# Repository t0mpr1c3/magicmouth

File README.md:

magicmouth
==========

Arduino speech shield http://www.tinyurl.com/magicmouth/

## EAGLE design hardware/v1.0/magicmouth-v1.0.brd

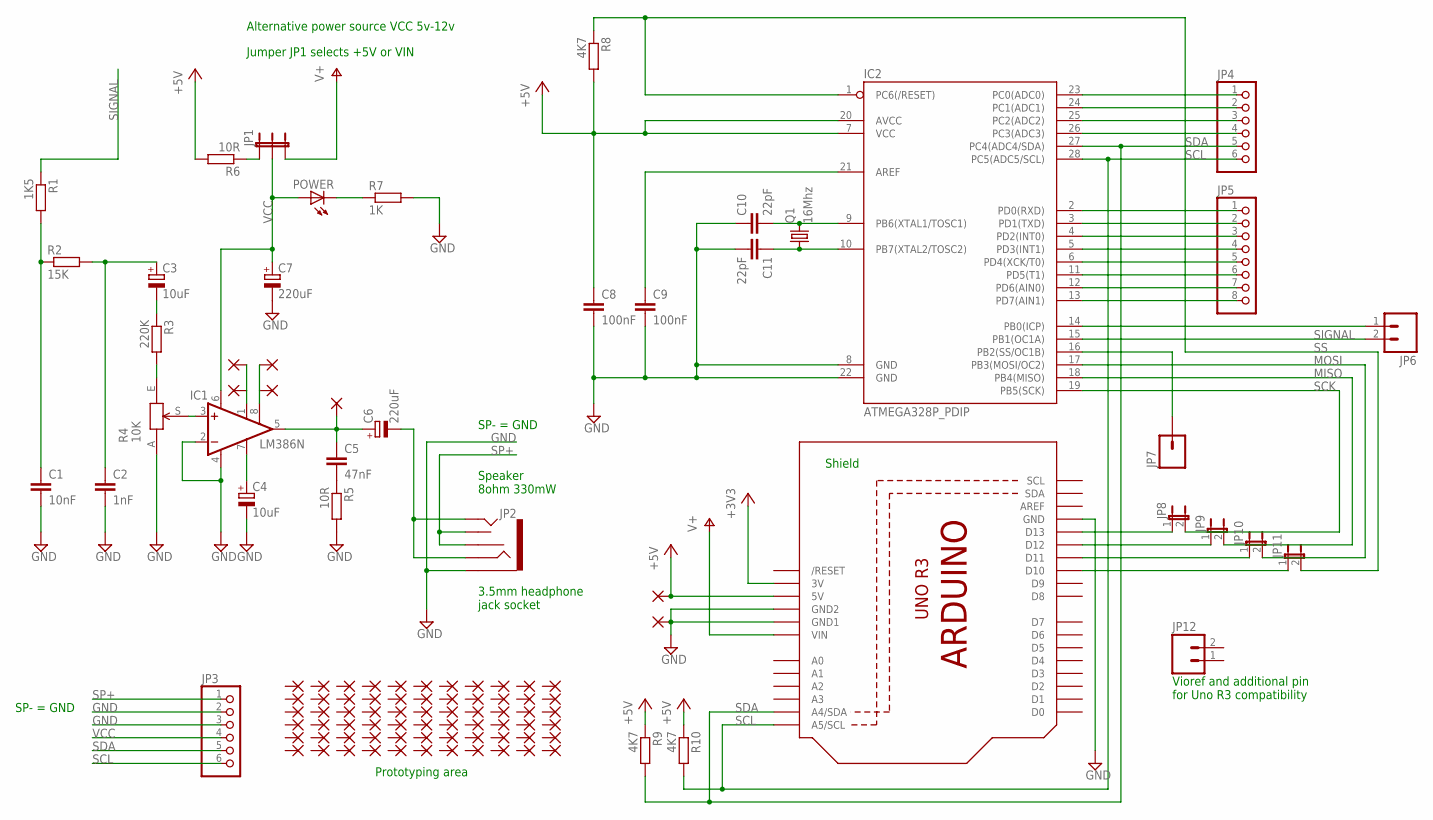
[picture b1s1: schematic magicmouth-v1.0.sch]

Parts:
C1: 10nF; C050-025X075
C2: 1nF; C050-025X075
C3, C4: 10uF; E2,5-7
C5: 47nF; C050-025X075
C6, C7: 220uF; TT2D7
C8, C9: 100nF; C025-025X050
C10, C11: 22pF; C025-025X050
IC1: LM386N; DIL08
IC2: ATMEGA328P_PDIP; DIL28-3
JP1: JUMPER-3PTH; 1X03
JP2: AUDIO-JACK2PTH; AUDIO-JACK
JP3, JP4: PINHD-1X6CB; 1X06-CLEANBIG
JP5: PINHD-1X8CLEANBIG; 1X08-CLEANBIG
JP6, JP12: M021X02_NO_SILK; 1X02_NO_SILK
JP7: M01SMDNS; 1X01NS
JP8, JP9, JP10, JP11: JUMPER-2PTH; 1X02
P1, P5, P8: 1,6/0,8
PAD1, PAD3, PAD7, PAD8, PAD9, PAD10, PAD11, PAD12, PAD13, PAD14, PAD15, PAD16, PAD17, PAD18, PAD19, PAD20, PAD21, PAD22, PAD23, PAD24, PAD25, PAD26, PAD27, PAD28, PAD29, PAD30, PAD31, PAD32, PAD33, PAD34, PAD35, PAD36, PAD37, PAD38, PAD39, PAD40, PAD41, PAD42, PAD43, PAD44, PAD45, PAD46, PAD47, PAD48, PAD49, PAD50, PAD51, PAD52, PAD53, PAD54, PAD55, PAD56, PAD57, PAD58, PAD59, PAD60, PAD61, PAD62, PAD63, PAD64, PAD65, PAD66, PAD67, PAD68, PAD69, PAD70, PAD71, PAD72, PAD73, PAD74: 1,6/0,8
POWER: LED3MM
Q1: 16Mhz; HC49/S
R1: 1K5; 0207/7
R2: 15K; 0207/7
R3: 220K; 0207/7
R4: 10K; 3352T
R5, R6: 10R; 0207/7
R7: 1K; 0207/7
R8, R9, R10: 4K7; 0207/7
U1: ARDUINOR3-NOIOREF-NOTEXT; ARDUINOR3-NOTEXT-NOIOREF

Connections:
+3V3: U1.3V
+5V: C8.1, IC2.7 (VCC), IC2.20 (AVCC), PAD55.1, R6.2, R8.2, R9.1, R10.1, U1.5V
D8: IC2.14 (PB0(ICP)), JP6.1
GND: C1.2, C2.2, C4.-, C7.-, C8.2, C9.2, C10.1, C11.2, IC1.2 (-IN), IC1.4 (GND), IC2.8 (GND), IC2.22 (GND), JP2.SLEEVE, JP3.2, JP3.3, PAD68.1, R4.A, R5.2, R7.2, U1.GND, U1.GND1, U1.GND2
MISO: IC2.18 (PB4(MISO)), JP9.2
MOSI: IC2.17 (PB3(MOSI/OC2)), JP10.2
unnamed: C5.1, C6.+, IC1.5 (OUT), P5.1
unnamed: C1.1, R1.2, R2.1
unnamed: C9.1, IC2.21 (AREF)
unnamed: C5.2, R5.1
unnamed: R3.2, R4.E
unnamed: C10.2, IC2.9 (PB6(XTAL1/TOSC1)), Q1.2
unnamed: JP1.1, R6.1
unnamed: C6.-, JP2.RING, JP2.TIP
unnamed: IC1.3 (+IN), R4.S
unnamed: POWER.K (C), R7.1
unnamed: C11.1, IC2.10 (PB7(XTAL2/TOSC2)), Q1.1
unnamed: IC2.16 (PB2(SS/OC1B)), JP7.1
unnamed: IC2.23 (PC0(ADC0)), JP4.1
unnamed: C2.1, C3.+, R2.2
unnamed: IC2.24 (PC1(ADC1)), JP4.2
unnamed: IC2.2 (PD0(RXD)), JP5.1
unnamed: IC2.3 (PD1(TXD)), JP5.2
unnamed: IC2.4 (PD2(INT0)), JP5.3
unnamed: IC2.5 (PD3(INT1)), JP5.4
unnamed: IC2.6 (PD4(XCK/T0)), JP5.5
unnamed: IC2.11 (PD5(T1)), JP5.6
unnamed: IC2.12 (PD6(AIN0)), JP5.7
unnamed: IC2.13 (PD7(AIN1)), JP5.8
unnamed: C4.+, IC1.7 (BYPASS)
unnamed: IC2.25 (PC2(ADC2)), JP4.3
unnamed: IC2.26 (PC3(ADC3)), JP4.4
unnamed: IC1.1 (GAIN), P1.1, PAD1.1
unnamed: C3.-, R3.1
unnamed: JP8.1, U1.D13
unnamed: JP9.1, U1.D12
unnamed: JP10.1, U1.D11
unnamed: JP11.1, U1.D10
unnamed: IC1.8 (GAIN), P8.1, PAD3.1
SCK: IC2.19 (PB5(SCK)), JP8.2
SCL: IC2.28 (PC5(ADC5/SCL)), JP3.6, JP4.6, R10.2, U1.A5 (A5/SCL)
SDA: IC2.27 (PC4(ADC4/SDA)), JP3.5, JP4.5, R9.2, U1.A4 (A4/SDA)
SIGNAL: IC2.15 (PB1(OC1A)), JP6.2, R1.1
SP+: JP2.RSH, JP2.TSH, JP3.1
SS: IC2.1 (PC6(/RESET)), JP11.2, R8.1
VCC: C7.+, IC1.6 (VS), JP1.2, JP3.4, POWER.A
VIN: JP1.3, U1.VIN

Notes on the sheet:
Speaker 8ohm 330mW
Jumper JP1 selects +5V or VIN
Alternative power source VCC 5v-12v
Shield
3.5mm headphone jack socket
Prototyping area
SP- = GND
Vioref and additional pin for Uno R3 compatibility

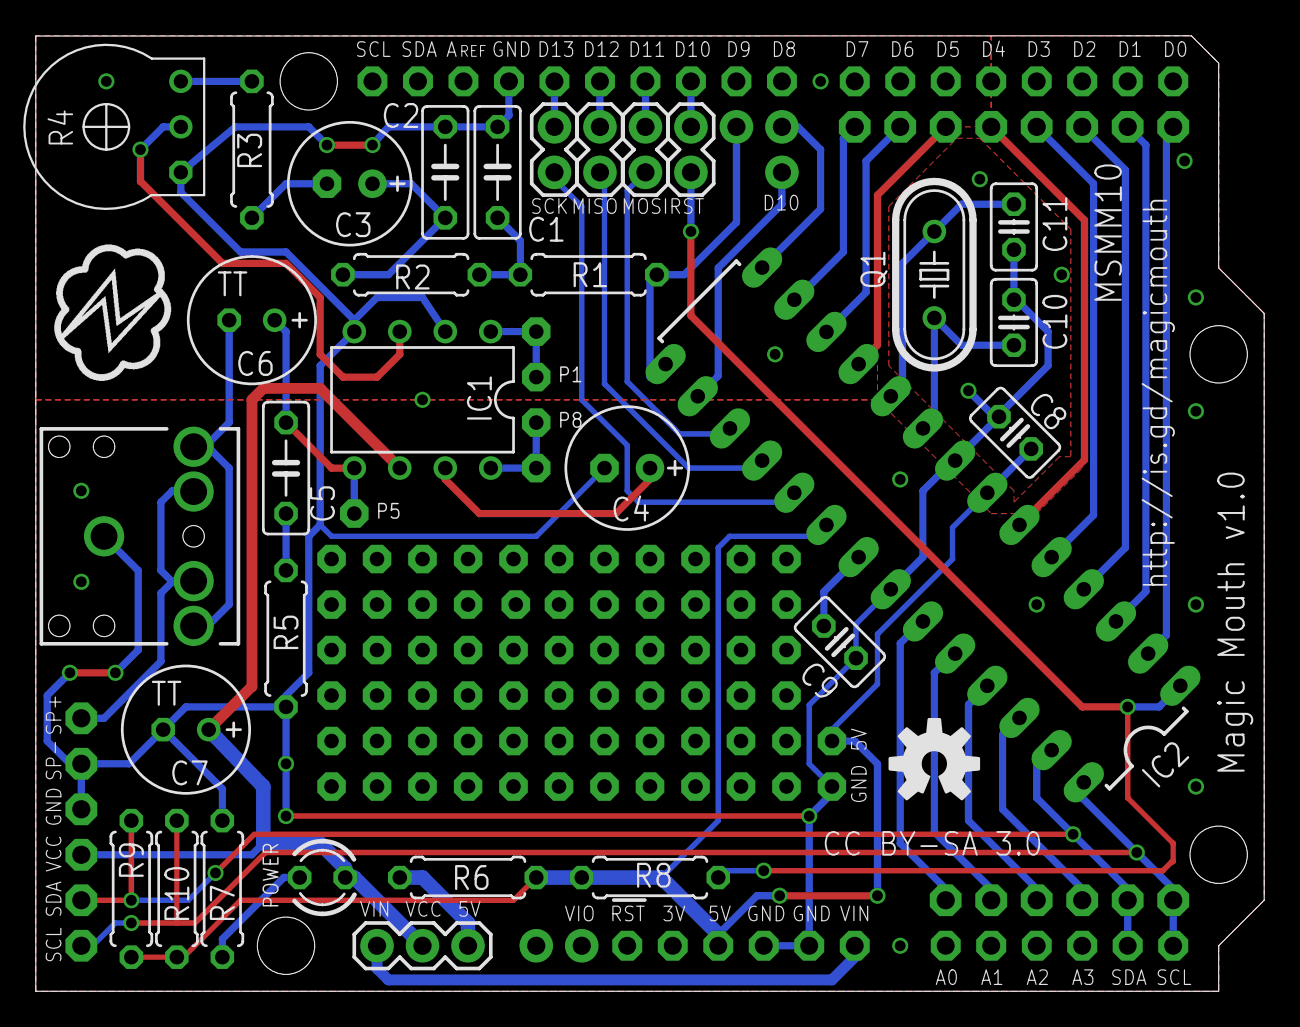
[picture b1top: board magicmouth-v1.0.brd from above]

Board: 2 copper layers, 68.6 x 53.3 mm, 113 parts (1 on the bottom side), 46 nets.

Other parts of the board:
U$1, U$2: OSHW-LOGO-M

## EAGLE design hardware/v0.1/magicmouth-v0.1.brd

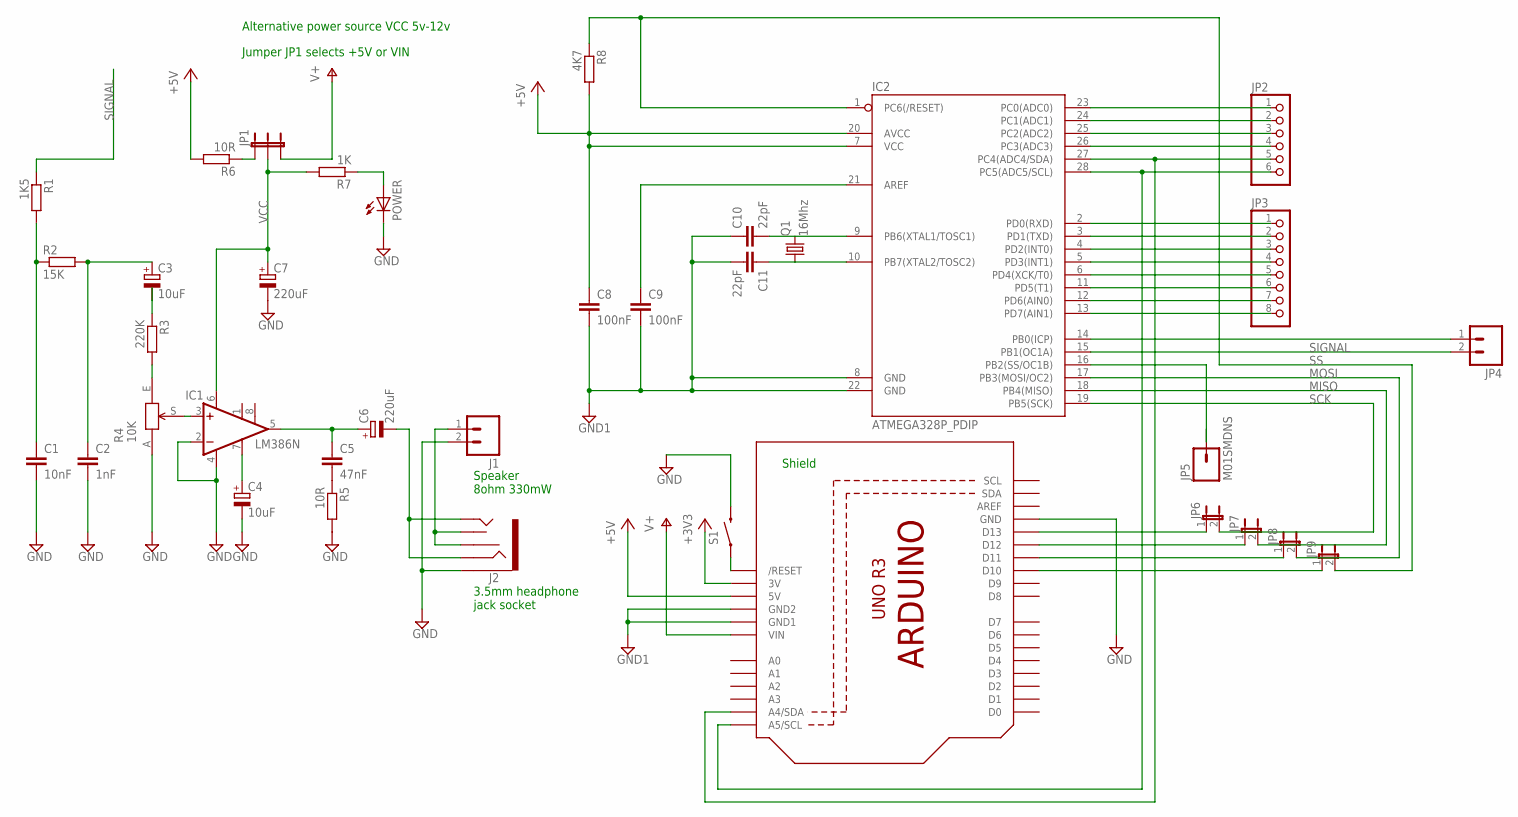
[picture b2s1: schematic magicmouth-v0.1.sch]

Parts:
C1: 10nF; C050-025X075
C2: 1nF; C050-025X075
C3, C4: 10uF; E2,5-7
C5: 47nF; C050-025X075
C6, C7: 220uF; TT5D7L
C8, C9: 100nF; C025-025X050
C10, C11: 22pF; C025-025X050
IC1: LM386N; DIL08
IC2: ATMEGA328P_PDIP; DIL28-3
J1: M023.5MM; SCREWTERMINAL-3.5MM-2
J2: AUDIO-JACK2PTH; AUDIO-JACK
JP1: JUMPER-3PTH; 1X03
JP2: PINHD-1X6CB; 1X06-CLEANBIG
JP3: PINHD-1X8CLEANBIG; 1X08-CLEANBIG
JP4: M021X02_NO_SILK; 1X02_NO_SILK
JP5: M01SMDNS; 1X01NS
JP6, JP7, JP8, JP9: JUMPER-2PTH; 1X02
POWER: LED3MM
Q1: 16Mhz; HC49/S
R1: 1K5; 0207/7
R2: 15K; 0207/7
R3: 220K; 0207/7
R4: 10K; 3352T
R5, R6: 10R; 0207/7
R7: 1K; 0207/7
R8: 4K7; 0207/7
S1: SWITCH-MOMENTARY-2PTH; TACTILE-PTH
U1: ARDUINOR3-NOIOREF-NOTEXT; ARDUINOR3-NOTEXT-NOIOREF

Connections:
+3V3: U1.3V
+5V: C8.1, IC2.7 (VCC), IC2.20 (AVCC), R6.2, R8.2, U1.5V
GND: C1.2, C2.2, C4.-, C7.-, IC1.2 (-IN), IC1.4 (GND), J1.2, J2.SLEEVE, POWER.K (C), R4.A, R5.2, S1.3 (2), U1.GND
GND1: C8.2, C9.2, C10.1, C11.2, IC2.8 (GND), IC2.22 (GND), U1.GND1, U1.GND2
MISO: IC2.18 (PB4(MISO)), JP7.2
MOSI: IC2.17 (PB3(MOSI/OC2)), JP8.2
unnamed: C5.1, C6.+, IC1.5 (OUT)
unnamed: C1.1, R1.2, R2.1
unnamed: J1.1, J2.RSH, J2.TSH
unnamed: C5.2, R5.1
unnamed: C3.-, R3.1
unnamed: C10.2, IC2.9 (PB6(XTAL1/TOSC1)), Q1.2
unnamed: JP1.1, R6.1
unnamed: C6.-, J2.RING, J2.TIP
unnamed: IC1.3 (+IN), R4.S
unnamed: POWER.A, R7.1
unnamed: C11.1, IC2.10 (PB7(XTAL2/TOSC2)), Q1.1
unnamed: IC2.16 (PB2(SS/OC1B)), JP5.1
unnamed: IC2.23 (PC0(ADC0)), JP2.1
unnamed: IC2.24 (PC1(ADC1)), JP2.2
unnamed: IC2.25 (PC2(ADC2)), JP2.3
unnamed: IC2.2 (PD0(RXD)), JP3.1
unnamed: IC2.3 (PD1(TXD)), JP3.2
unnamed: IC2.4 (PD2(INT0)), JP3.3
unnamed: IC2.5 (PD3(INT1)), JP3.4
unnamed: IC2.6 (PD4(XCK/T0)), JP3.5
unnamed: IC2.11 (PD5(T1)), JP3.6
unnamed: IC2.12 (PD6(AIN0)), JP3.7
unnamed: IC2.13 (PD7(AIN1)), JP3.8
unnamed: IC2.14 (PB0(ICP)), JP4.1
unnamed: JP6.1, U1.D13
unnamed: JP7.1, U1.D12
unnamed: IC2.26 (PC3(ADC3)), JP2.4
unnamed: JP8.1, U1.D11
unnamed: JP9.1, U1.D10
unnamed: IC2.27 (PC4(ADC4/SDA)), JP2.5, U1.A4 (A4/SDA)
unnamed: IC2.28 (PC5(ADC5/SCL)), JP2.6, U1.A5 (A5/SCL)
unnamed: C2.1, C3.+, R2.2
unnamed: C4.+, IC1.7 (BYPASS)
unnamed: C9.1, IC2.21 (AREF)
unnamed: S1.1, U1.RESET (/RESET)
unnamed: R3.2, R4.E
SCK: IC2.19 (PB5(SCK)), JP6.2
SIGNAL: IC2.15 (PB1(OC1A)), JP4.2, R1.1
SS: IC2.1 (PC6(/RESET)), JP9.2, R8.1
VCC: C7.+, IC1.6 (VS), JP1.2, R7.2
VIN: JP1.3, U1.VIN

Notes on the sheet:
Speaker 8ohm 330mW
Jumper JP1 selects +5V or VIN
Alternative power source VCC 5v-12v
Shield
3.5mm headphone jack socket

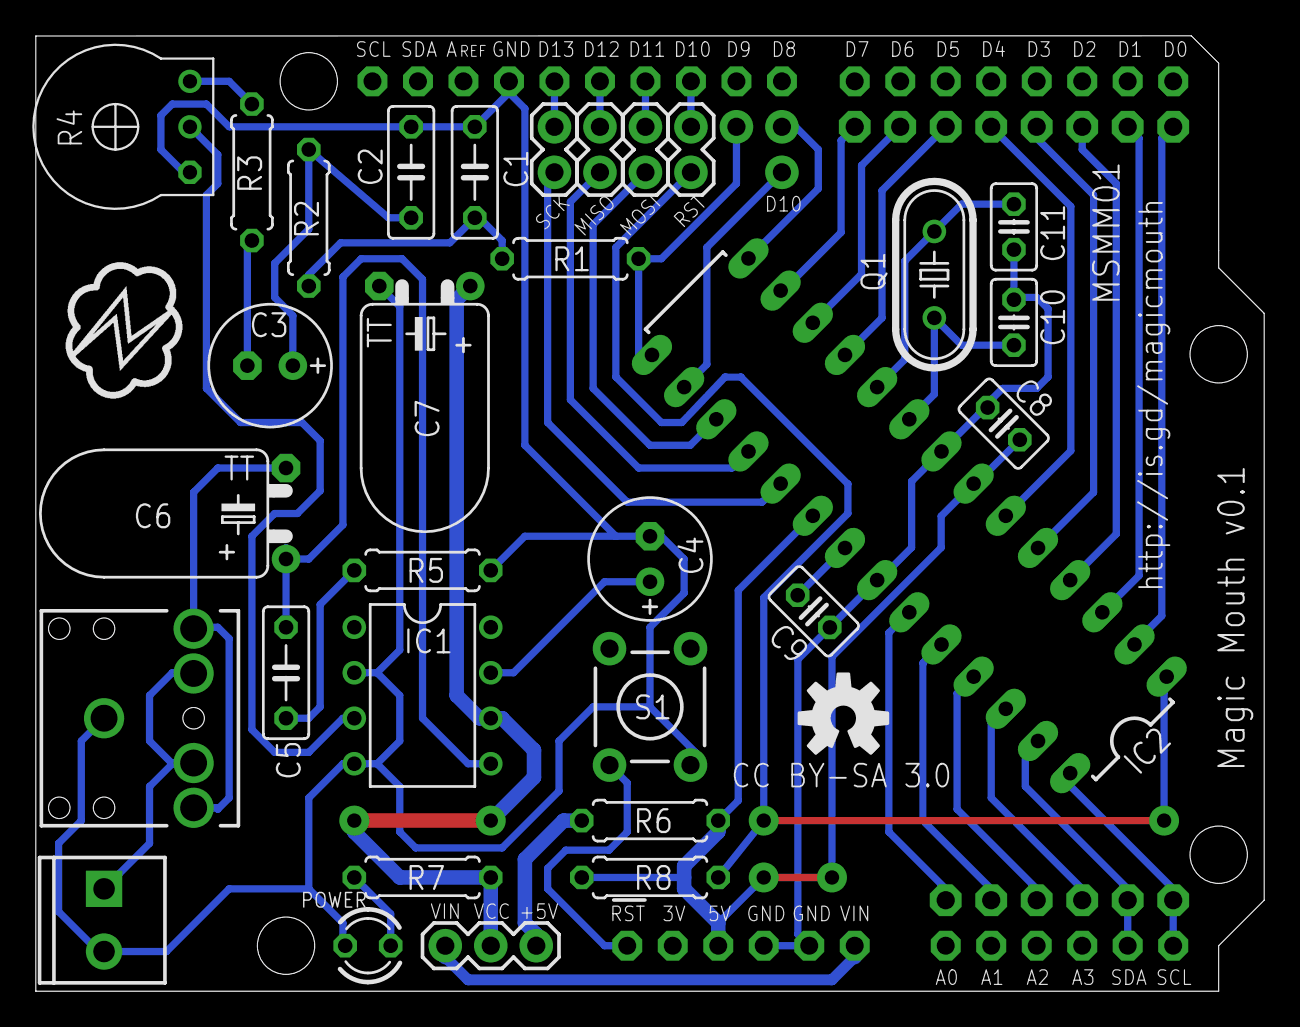
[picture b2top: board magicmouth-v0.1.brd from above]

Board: 2 copper layers, 68.6 x 53.3 mm, 37 parts (0 on the bottom side), 46 nets.

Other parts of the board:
U$1: OSHW-LOGO-M

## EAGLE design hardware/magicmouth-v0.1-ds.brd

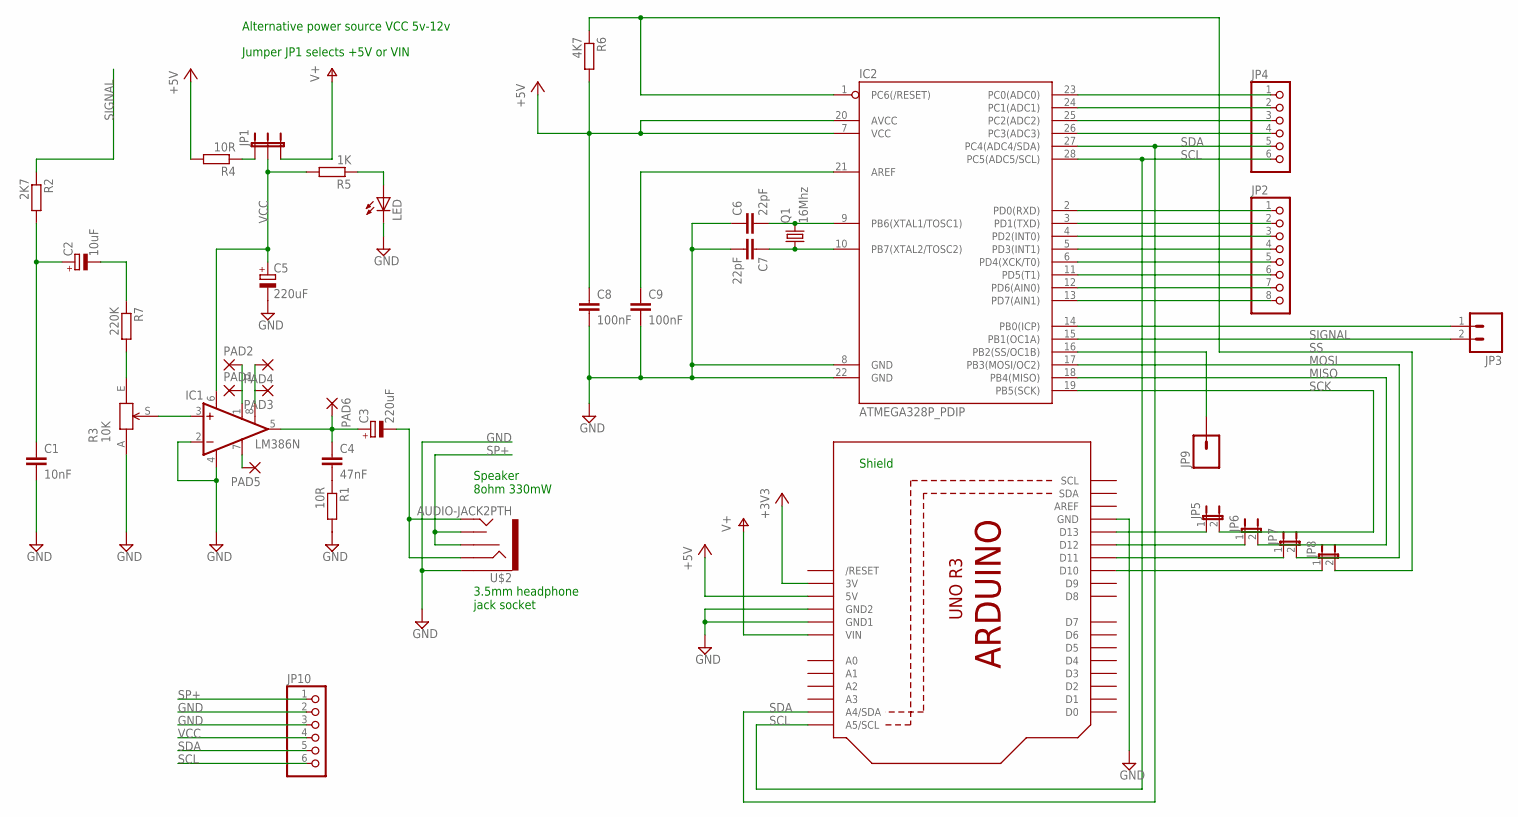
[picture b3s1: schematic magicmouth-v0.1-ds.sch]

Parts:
C1: 10nF; C050-025X075
C2: 10uF; E2,5-7
C3, C5: 220uF; TT2D7
C4: 47nF; C050-025X075
C6, C7: 22pF; C025-025X050
C8, C9: 100nF; C025-025X050
IC1: LM386N; DIL08
IC2: ATMEGA328P_PDIP; DIL28-3
JP1: JUMPER-3PTH; 1X03
JP2: PINHD-1X8CLEANBIG; 1X08-CLEANBIG
JP3: M021X02_NO_SILK; 1X02_NO_SILK
JP4, JP10: PINHD-1X6CB; 1X06-CLEANBIG
JP5, JP6, JP7, JP8: JUMPER-2PTH; 1X02
JP9: M01SMDNS; 1X01NS
LED: LED3MM
PAD1, PAD2, PAD3, PAD4, PAD5, PAD6: 1,6/0,8
Q1: 16Mhz; HC49/S
R1, R4: 10R; 0207/7
R2: 2K7; 0207/7
R3: 10K; 3352T
R5: 1K; 0207/7
R6: 4K7; 0207/7
R7: 220K; 0207/7
U1: ARDUINOR3-NOIOREF-NOTEXT; ARDUINOR3-NOTEXT-NOIOREF
U$2: AUDIO-JACK2PTH; AUDIO-JACK

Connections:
+3V3: U1.3V
+5V: C8.1, IC2.7 (VCC), IC2.20 (AVCC), R4.2, R6.2, U1.5V
D8: IC2.14 (PB0(ICP)), JP3.1
GND: C1.2, C5.-, C6.1, C7.2, C8.2, C9.2, IC1.2 (-IN), IC1.4 (GND), IC2.8 (GND), IC2.22 (GND), JP10.2, JP10.3, LED.K (C), R1.2, R3.A, U1.GND, U1.GND1, U1.GND2, U$2.SLEEVE
MISO: IC2.18 (PB4(MISO)), JP6.2
MOSI: IC2.17 (PB3(MOSI/OC2)), JP7.2
unnamed: C3.+, C4.1, IC1.5 (OUT), PAD6.1
unnamed: C1.1, C2.+, R2.2
unnamed: C9.1, IC2.21 (AREF)
unnamed: C4.2, R1.1
unnamed: R3.E, R7.2
unnamed: C6.2, IC2.9 (PB6(XTAL1/TOSC1)), Q1.2
unnamed: JP1.1, R4.1
unnamed: C3.-, U$2.RING, U$2.TIP
unnamed: IC1.3 (+IN), R3.S
unnamed: LED.A, R5.1
unnamed: C7.1, IC2.10 (PB7(XTAL2/TOSC2)), Q1.1
unnamed: IC2.16 (PB2(SS/OC1B)), JP9.1
unnamed: IC2.23 (PC0(ADC0)), JP4.1
unnamed: IC2.24 (PC1(ADC1)), JP4.2
unnamed: IC2.2 (PD0(RXD)), JP2.1
unnamed: IC2.3 (PD1(TXD)), JP2.2
unnamed: IC2.4 (PD2(INT0)), JP2.3
unnamed: IC2.5 (PD3(INT1)), JP2.4
unnamed: IC2.6 (PD4(XCK/T0)), JP2.5
unnamed: IC2.11 (PD5(T1)), JP2.6
unnamed: IC2.12 (PD6(AIN0)), JP2.7
unnamed: IC2.13 (PD7(AIN1)), JP2.8
unnamed: IC2.25 (PC2(ADC2)), JP4.3
unnamed: IC2.26 (PC3(ADC3)), JP4.4
unnamed: IC1.1 (GAIN), PAD1.1, PAD2.1
unnamed: C2.-, R7.1
unnamed: JP5.1, U1.D13
unnamed: JP6.1, U1.D12
unnamed: JP7.1, U1.D11
unnamed: JP8.1, U1.D10
unnamed: IC1.7 (BYPASS), PAD5.1
unnamed: IC1.8 (GAIN), PAD3.1, PAD4.1
SCK: IC2.19 (PB5(SCK)), JP5.2
SCL: IC2.28 (PC5(ADC5/SCL)), JP4.6, JP10.6, U1.A5 (A5/SCL)
SDA: IC2.27 (PC4(ADC4/SDA)), JP4.5, JP10.5, U1.A4 (A4/SDA)
SIGNAL: IC2.15 (PB1(OC1A)), JP3.2, R2.1
SP+: JP10.1, U$2.RSH, U$2.TSH
SS: IC2.1 (PC6(/RESET)), JP8.2, R6.1
VCC: C5.+, IC1.6 (VS), JP1.2, JP10.4, R5.2
VIN: JP1.3, U1.VIN

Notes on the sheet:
Speaker 8ohm 330mW
Jumper JP1 selects +5V or VIN
Alternative power source VCC 5v-12v
Shield
3.5mm headphone jack socket

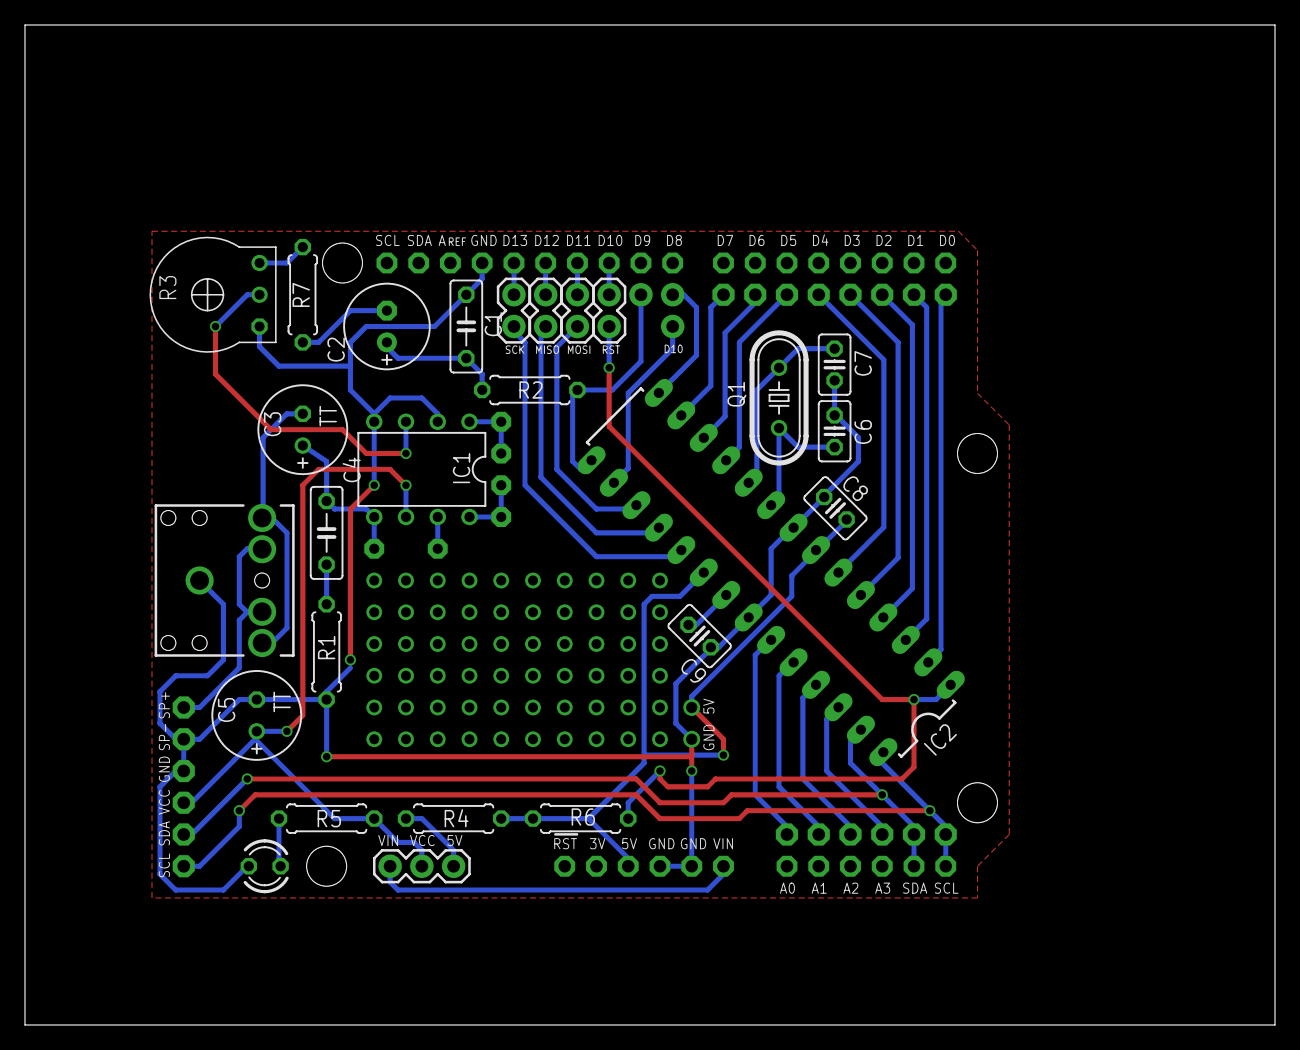
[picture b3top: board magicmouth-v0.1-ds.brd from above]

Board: 2 copper layers, 100.0 x 80.0 mm, 39 parts (0 on the bottom side), 45 nets.

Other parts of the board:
U$1: OSHWLOGO_TOL_0.2

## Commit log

2012-11-28 magicmouth-v0.1 eagle files and webbotlib project file
2012-11-30 added 5V jumper to v0.1 single sided board
    added 5V jumper to v0.1 single sided board
    added 5V jumper to v0.1 single sided board
    added 5V jumper to v0.1 single sided board
    added 5V jumper to v0.1 single sided board
2012-12-04 added programming jumpers
2012-12-05 reset switch on ss board; optional capacitor
2012-12-10 220K resistor in series with gain control
2012-12-14 connected reset button to GND not +5V
2012-12-18 vertical 220uF caps, 6 pin IO header
2012-12-18 adjusted placement to avoid through holes directly above Arduino USB port
2012-12-19 substituted atmega328p, added logo
2012-12-20 trace corrections
2012-12-20 v0.1 and v1.0 eagle files
2012-12-20 wide power traces, toner transfer images
2012-12-20 v0.1-ss and v0.1-ds removed
2012-12-21 10uf bypass cap for LM386
2012-12-21 updated toner transfer images
2012-12-21 vias, isolated ground planes around crystal, gerbers
2012-12-23 firmware initial commit
2013-01-05 pullup resistors on SDA and SCL
2013-01-31 adjusted position of trimpot, enlarged small text
2013-02-01 copied magic smoke logo on bottom
2013-02-01 change text size for SCK on bottom

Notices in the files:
hardware/magicmouth-v0.1-ds.brd:
CC BY-SA 3.0
parts and their libraries:
SparkFun-Connectors: Licensing: CC v3.0 Share-Alike You are welcome to use this library for commercial purposes.
